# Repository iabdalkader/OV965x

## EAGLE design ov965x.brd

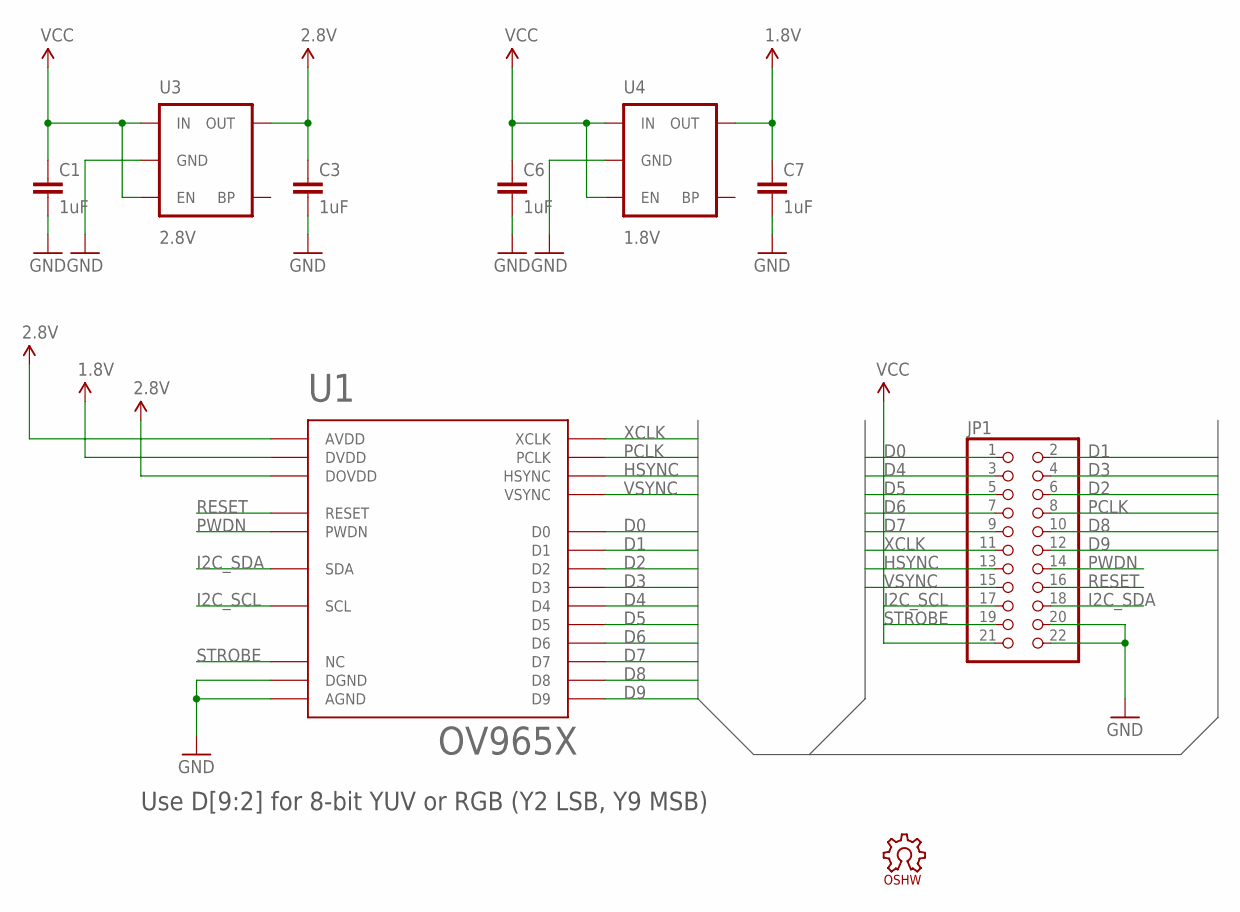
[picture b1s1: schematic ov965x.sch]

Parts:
C1, C3, C6, C7: 1uF; 0402-CAP
JP1: PINHD-2X11; 2X11
LOGO1: OSHW_LOGO_6MILX0150-NT; OSHW_6X150_NOTEXT
U1: OV965X
U3: 2.8V; SOT23-5
U4: 1.8V; SOT23-5

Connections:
1.8V: C7.1, U1.P$10 (DVDD), U4.5 (OUT)
2.8V: C3.1, U1.P$4 (AVDD), U1.P$11 (DOVDD), U3.5 (OUT)
D0: JP1.1, U1.P$24 (D0)
D1: JP1.2, U1.P$23 (D1)
D2: JP1.6, U1.P$19 (D2)
D3: JP1.4, U1.P$21 (D3)
D4: JP1.3, U1.P$22 (D4)
D5: JP1.5, U1.P$20 (D5)
D6: JP1.7, U1.P$18 (D6)
D7: JP1.9, U1.P$16 (D7)
D8: JP1.10, U1.P$14 (D8)
D9: JP1.12, U1.P$12 (D9)
GND: C1.2, C3.2, C6.2, C7.2, JP1.20, JP1.22, U1.P$2 (AGND), U1.P$15 (DGND), U3.2 (GND), U4.2 (GND)
HSYNC: JP1.13, U1.P$9 (HSYNC)
I2C_SCL: JP1.17, U1.P$5 (SCL)
I2C_SDA: JP1.18, U1.P$3 (SDA)
PCLK: JP1.8, U1.P$17 (PCLK)
PWDN: JP1.14, U1.P$8 (PWDN)
RESET: JP1.16, U1.P$6 (RESET)
STROBE: JP1.19, U1.P$1 (NC)
VCC: C1.1, C6.1, JP1.21, U3.1 (IN), U3.3 (EN), U4.1 (IN), U4.3 (EN)
VSYNC: JP1.15, U1.P$7 (VSYNC)
XCLK: JP1.11, U1.P$13 (XCLK)

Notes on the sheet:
Use D[9:2] for 8-bit YUV or RGB (Y2 LSB, Y9 MSB)

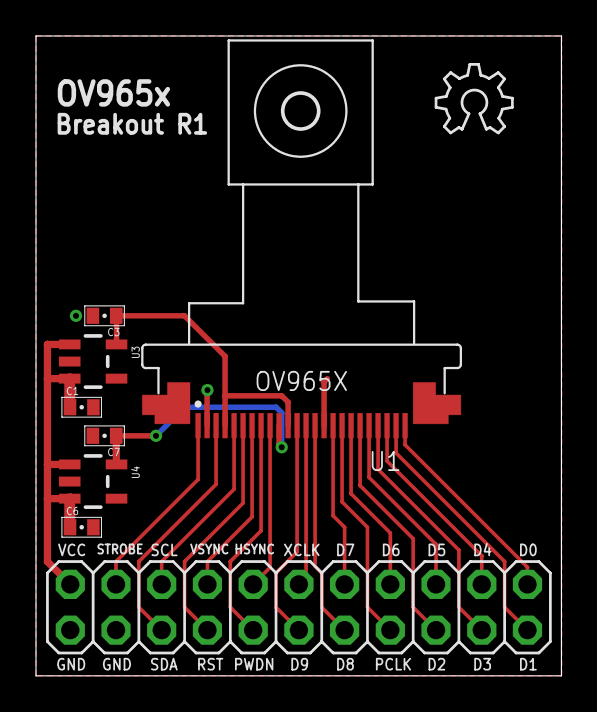
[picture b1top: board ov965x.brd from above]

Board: 2 copper layers, 29.2 x 35.5 mm, 9 parts (0 on the bottom side), 23 nets.
